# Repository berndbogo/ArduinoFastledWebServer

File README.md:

# ArduinoFastledWebServer

--> Arduino
--> WS2811 
--> FastLED
--> WebServer

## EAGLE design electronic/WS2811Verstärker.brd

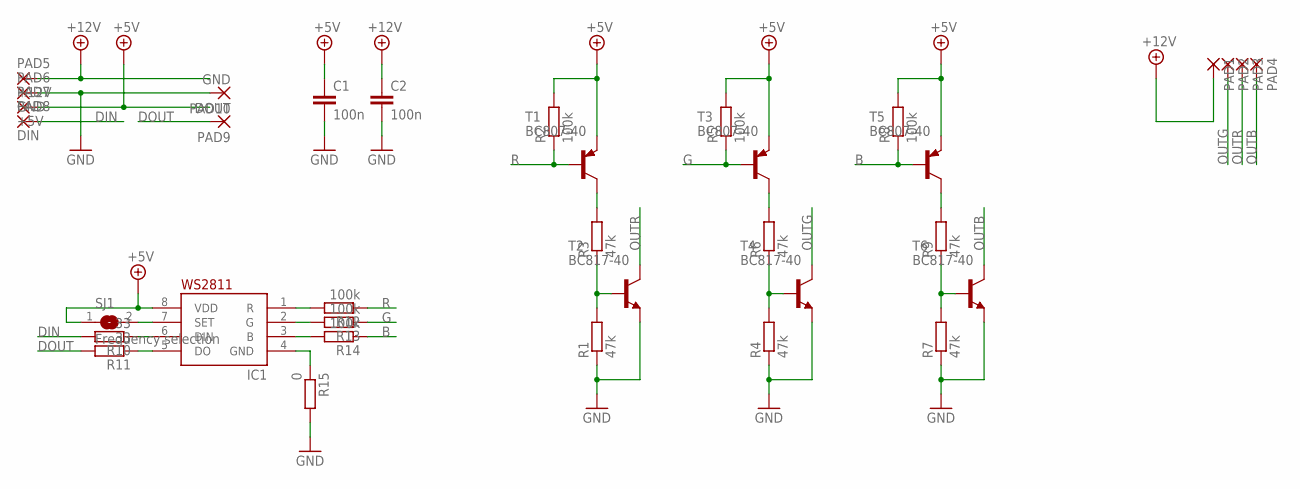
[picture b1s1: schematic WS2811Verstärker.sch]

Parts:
C1, C2: 100n; C1206
IC1: WS2811-SOP8; SO08-SKINNYPADS
PAD1, PAD2, PAD3, PAD4: SMD5; SMD2,54-5,08
PAD5: +12V; SMD2,54-5,08
PAD6, PAD10: GND; SMD2,54-5,08
PAD7: +5V; SMD2,54-5,08
PAD8: DIN; SMD2,54-5,08
PAD9: DOUT; SMD2,54-5,08
R1, R3, R4, R6, R7, R9: 47k; R1206
R2, R5, R8, R12, R13, R14: 100k; R1206
R10, R11: 33; R1206
R15: 0; R1206
SJ1: Frequency selection; SJ
T1, T3, T5: BC807-40; SOT23-BEC
T2, T4, T6: BC817-40; SOT23-BEC

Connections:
+5V: C1.1, IC1.8 (VDD), PAD7.1, R2.2, R5.2, R8.2, SJ1.1, T1.E, T3.E, T5.E
+12V: C2.1, PAD1.1, PAD5.1
B: R8.1, R14.1, T5.B
DIN: PAD8.1, R10.2
DOUT: PAD9.1, R11.2
G: R5.1, R13.1, T3.B
GND: C1.2, C2.2, PAD6.1, PAD10.1, R1.1, R4.1, R7.1, R15.2, T2.E, T4.E, T6.E
unnamed: R1.2, R3.1, T2.B
unnamed: R3.2, T1.C
unnamed: IC1.7 (SET), SJ1.2
unnamed: R4.2, R6.1, T4.B
unnamed: R6.2, T3.C
unnamed: IC1.6 (DIN), R10.1
unnamed: R7.2, R9.1, T6.B
unnamed: R9.2, T5.C
unnamed: IC1.5 (DO), R11.1
unnamed: IC1.1 (R), R12.2
unnamed: IC1.2 (G), R13.2
unnamed: IC1.3 (B), R14.2
unnamed: IC1.4 (GND), R15.1
OUTB: PAD4.1, T6.C
OUTG: PAD2.1, T4.C
OUTR: PAD3.1, T2.C
R: R2.1, R12.1, T1.B

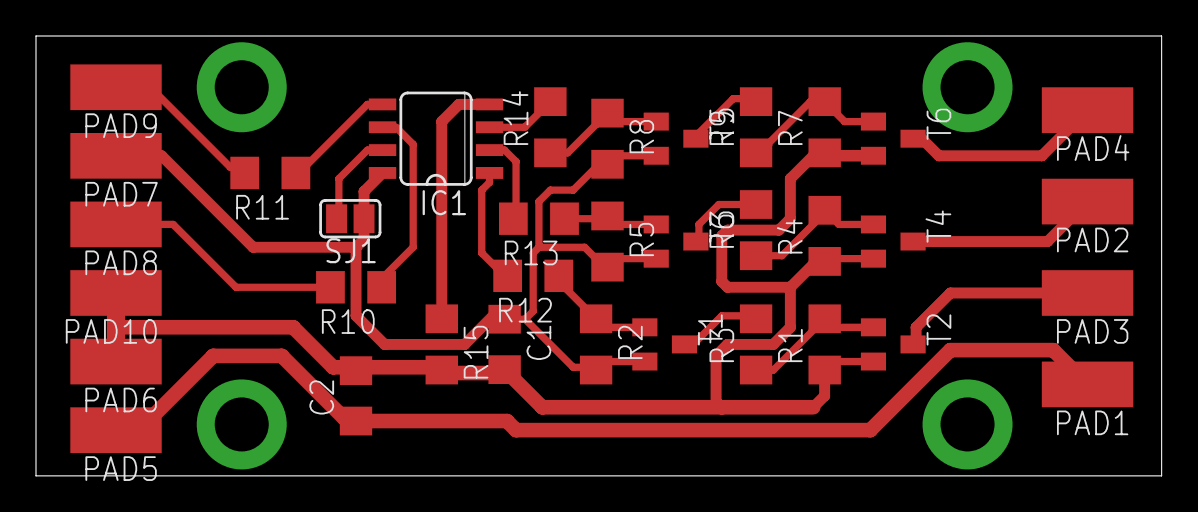
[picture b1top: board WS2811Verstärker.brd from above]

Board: 2 copper layers, 62.5 x 24.4 mm, 35 parts (0 on the bottom side), 24 nets.

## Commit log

2016-02-15 add WebServer.ino
2016-02-15 +folder
2016-02-15 ADD Layout
2016-02-15 triColor
2016-02-15 add multiColor
2016-02-15 cmmt
2016-02-16 customize NUM_LEDS_PIN_1 = 24 for testing the stair lights
    standard mode = tri with triC1 = 0xee6146, triC2 = 0x75af1d, triC3 = 0xffffff;
2016-02-16 change start colors
2016-02-17 add rainbow effects rainbow demo_mode() should be interruptible while the mode is active
2016-02-18 visualizer
2016-02-18 WS2811 EAGLE files
